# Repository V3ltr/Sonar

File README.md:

# Sonar

This is a simple distance detector. i works by sending out untrasonic sounds to sense if a object is in front of it.
Its very similar to the detecors cars use when you go in reverse and it starts screaming when you get close to a wall.
It uses very little battery but it doesnt have one build in so you have to plug it in.
On the display you see a green dot (thats you) and a red dot infront of you (thats a wall/object in your path) it also shows how far the object is and it works in the dark too!

[BOM.csv]
Part,Qty,Unit,Total,Vendor,Link
PCB,1,$15.52,$15.52,JLCPCB,https://cart.jlcpcb.com/quote?stencilLayer=2&stencilWidth=100&stencilLength=100&stencilCounts=5&plateType=1&spm=Jlcpcb.Homepage.1010
TFT IPS Color Display,1,$6.78,$6.78,LaskaKit,https://www.laskakit.cz/en/1-3--240x240-tft-ips-barevny-displej-st7789--spi/
ESP-WROOM-32,1,$5.91,$5.91,Dratek,https://dratek.cz/arduino-platforma/2062-esp-wroom-32-wifi-wlan-bluetooth-modul.html
Resistor 10uF 50V,1,$0.05,$0.05,Dratek,https://dratek.cz/arduino-platforma/7824-kondenzator-10uf-50v.html
HC-SR04,1,$1.74,$1.74,Alegro,https://allegro.cz/nabidka/meric-vzdalenosti-hc-sr04-arduino-16403683618
SMD 0805 0.1uF 100nF 50V X7R,1,$2.29,$2.29,Alegro,https://allegro.cz/nabidka/kondenzator-smd-0805-0-1uf-100nf-50v-x7r-40ks-12673411330
USB-C port,1,$1.83,$1.83,Alegro,https://allegro.cz/produkt/usb-c-konektor-se-gniazdo-usb-typ-c-24pin-de6395da-ec4c-4ab4-8fdd-8b11984ef204?offerId=18127435664&context=bc9e75cf9e1072ea5b6d449215016a9fe50400cc71a4111c6e22b5e38723b136c47bbfd7f15608bbd13475143a898e16f30f45c720e4db4f1668d6c03fd51fda82caa4bde1c3fb37e3557e51585e1b1e29cd5b376e028a793d9926ac79e48f9ce496418bc367e8ea314a2f1afb63058fb81779aabac3e0bba1eaa33e553ab57b6f26cf2b3b7007c270909831e91e4545&sellerHasChanged=false
Tax & shipping,$10.63,,,,

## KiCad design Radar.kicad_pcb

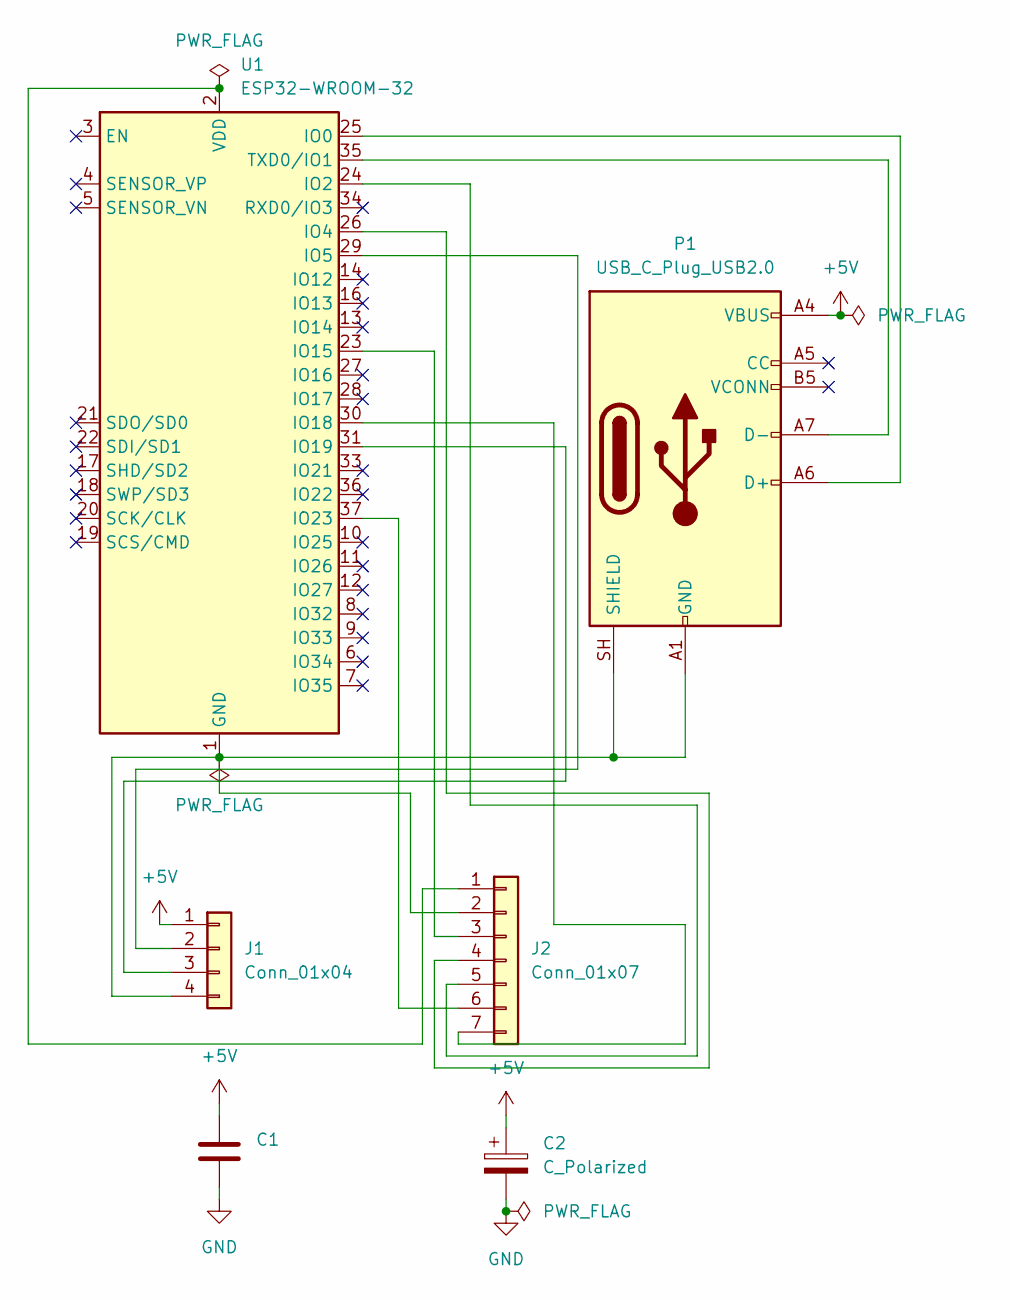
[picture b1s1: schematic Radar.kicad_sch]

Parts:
C1: C; C_0805_2012Metric
C2: C_Polarized; CP_Elec_4x5.3
J1: Conn_01x04; PinHeader_1x04_P2.54mm_Vertical
J2: Conn_01x07; PinHeader_1x07_P2.54mm_Vertical
P1: USB_C_Plug_USB2.0; USB_C_Receptacle_HRO_TYPE-C-31-M-12
U1: ESP32-WROOM-32

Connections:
+5V: C1.1, C2.1, J1.1, P1.A4 (VBUS), P1.A9 (VBUS), P1.B4 (VBUS), P1.B9 (VBUS)
GND: C1.2, C2.2
unnamed: J1.2, U1.29 (IO5)
unnamed: J1.3, U1.31 (IO19)
unnamed: J1.4, J2.2, P1.A1 (GND), P1.A12 (GND), P1.B1 (GND), P1.B12 (GND), P1.SH (SHIELD), U1.1 (GND), U1.15 (GND), U1.38 (GND), U1.39 (GND)
unnamed: J2.1, U1.2 (VDD)
unnamed: J2.3, U1.23 (IO15)
unnamed: J2.4, U1.26 (IO4)
unnamed: J2.5, U1.24 (IO2)
unnamed: J2.6, U1.37 (IO23)
unnamed: J2.7, U1.30 (IO18)
unnamed: P1.A6 (D+), U1.25 (IO0)
unnamed: P1.A7 (D-), U1.35 (TXD0/IO1)

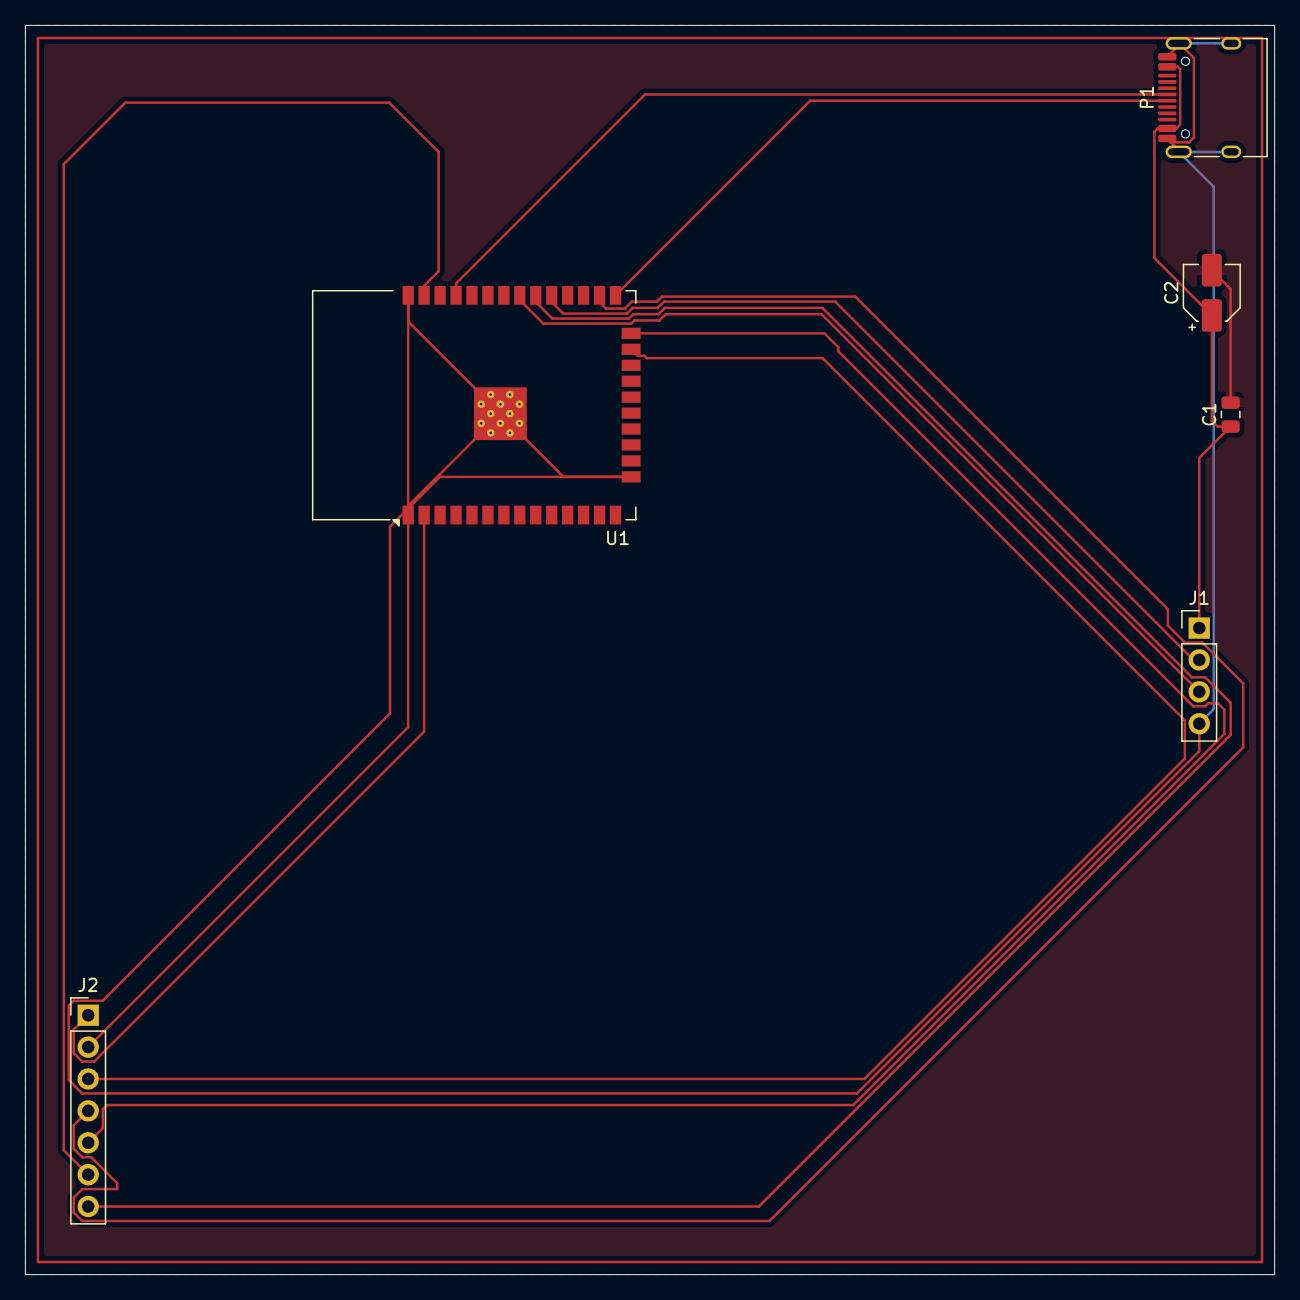
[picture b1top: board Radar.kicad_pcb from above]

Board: 2 copper layers, 99.5 x 99.5 mm, 6 parts (0 on the bottom side), 13 nets.
